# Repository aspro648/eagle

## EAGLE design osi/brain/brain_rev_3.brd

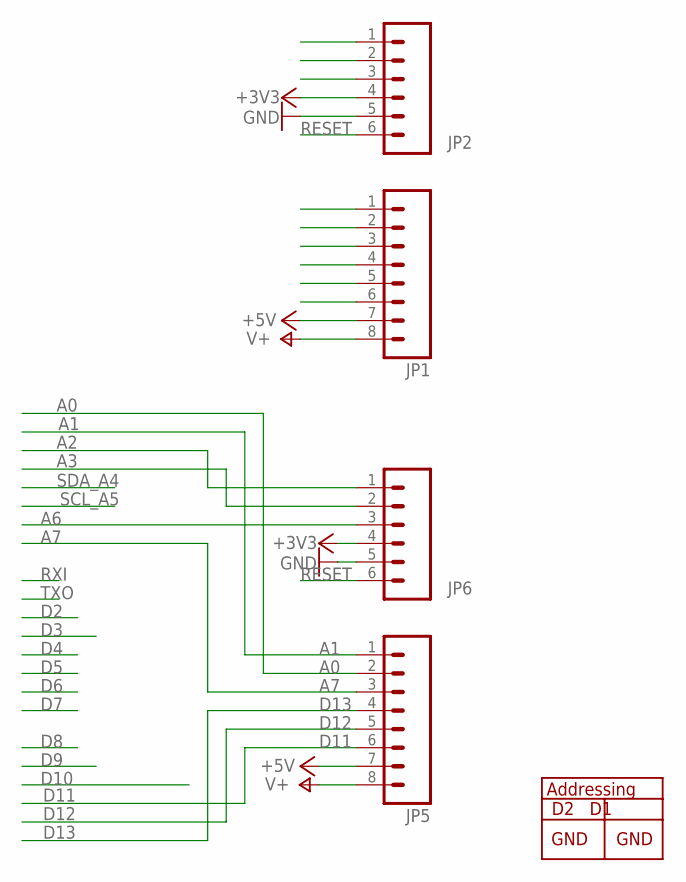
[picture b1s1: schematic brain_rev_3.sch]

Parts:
JP1, JP5: M081X08; 1X08
JP2, JP6: M06SIP; 1X06

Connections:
+3V3: JP2.4, JP6.4
+5V: JP1.7, JP5.7
A0: JP5.2
A1: JP5.1
A2: JP6.1
A3: JP6.2
A6: JP6.3
A7: JP5.3
D11: JP5.6
D12: JP5.5
D13: JP5.4
GND: JP2.5, JP6.5
RESET: JP2.6, JP6.6
V+: JP1.8, JP5.8

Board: 2 copper layers, 4 parts (0 on the bottom side), 5 nets, no tracks yet.

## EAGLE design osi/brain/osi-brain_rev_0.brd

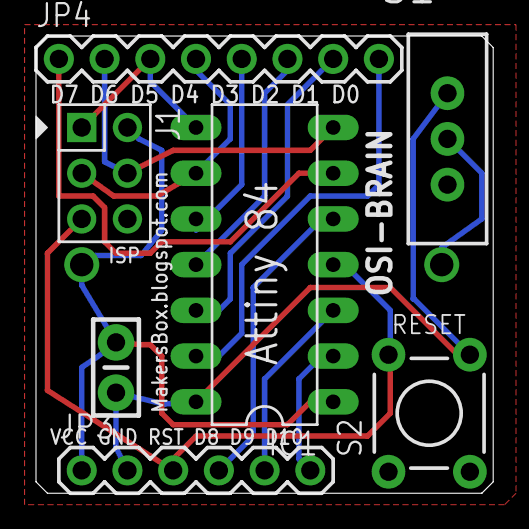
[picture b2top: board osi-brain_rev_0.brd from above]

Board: 2 copper layers, 25.4 x 25.4 mm, 8 parts (0 on the bottom side), 15 nets.

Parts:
BAT: BATTCOM_20MM_PTH
C1: CAP-PTH-SMALL-KIT
IC1: TINY24/44/84-PU; DIL14
J1: CON_HEADER_PRG_AVR_ICSP-PTH; HEADER_PRG_2X03
JP3: 1X06
JP4: 1X08
S1: SWITCH-SPDT
S2: TACTILE-PTH

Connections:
D0: IC1.13, JP4.8
D1: IC1.12, JP4.7
D2: IC1.11, JP4.6
D3: IC1.10, JP4.5
D4: IC1.9, J1.3, JP4.4
D5: IC1.8, J1.1, JP4.3
D6: IC1.7, J1.4, JP4.2
D7: IC1.6, JP4.1
D8: IC1.5, JP3.4
D9: IC1.3, JP3.5
D10: IC1.2, JP3.6
GND: C1.1, IC1.14, JP3.2, S1.1, S2.4
unnamed: BAT.1, S1.2
RESET: IC1.4, J1.5, JP3.3, S2.2
VCC: BAT.2, C1.2, IC1.1, J1.2, JP3.1

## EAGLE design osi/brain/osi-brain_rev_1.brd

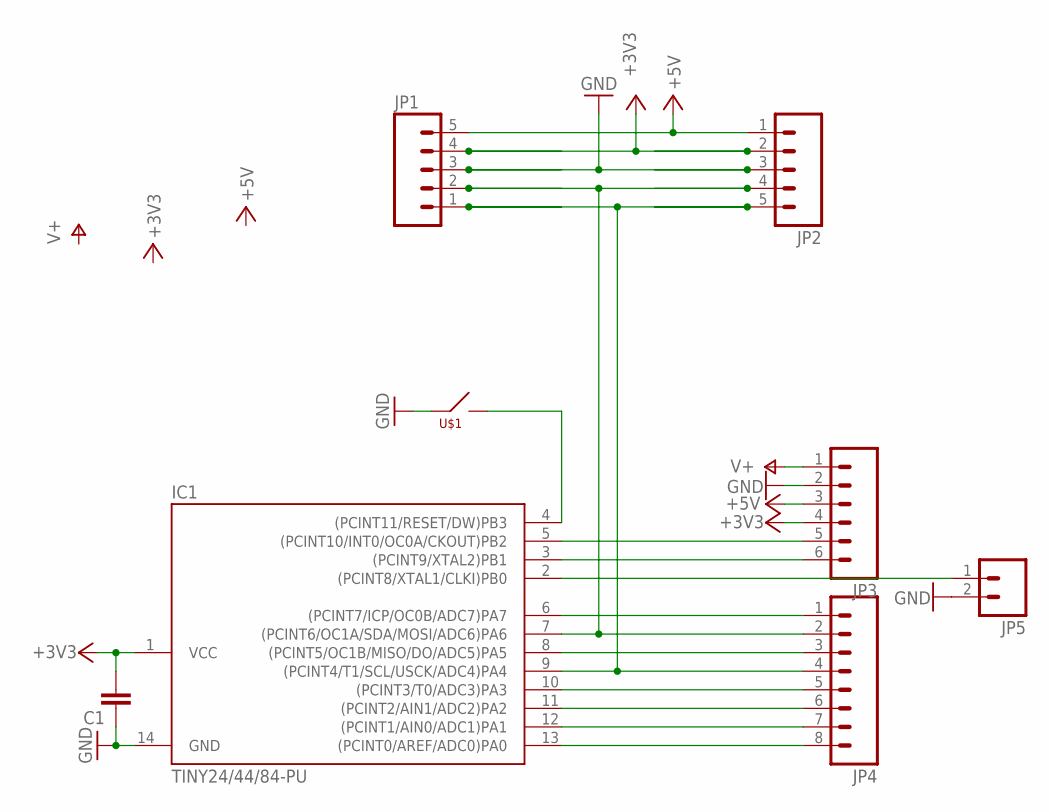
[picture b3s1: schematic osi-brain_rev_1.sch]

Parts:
C1: CAPKIT; CAP-PTH-SMALL-KIT
IC1: TINY24/44/84-PU; DIL14
JP1, JP2: M05PTH; 1X05
JP3: M06SIP; 1X06
JP4: M081X08; 1X08
JP5: M021X02_NO_SILK; 1X02_NO_SILK
U$1: PTS635_SWITCH

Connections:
+3V3: C1.2, IC1.1 (VCC), JP1.4, JP2.2, JP3.4
+5V: JP1.5, JP2.1, JP3.3
AREF_D0: IC1.13 ((PCINT0/AREF/ADC0)PA0), JP4.8
D1: IC1.12 ((PCINT1/AIN0/ADC1)PA1), JP4.7
D2: IC1.11 ((PCINT2/AIN1/ADC2)PA2), JP4.6
D3: IC1.10 ((PCINT3/T0/ADC3)PA3), JP4.5
D5: IC1.8 ((PCINT5/OC1B/MISO/DO/ADC5)PA5), JP4.3
D7: IC1.6 ((PCINT7/ICP/OC0B/ADC7)PA7), JP4.1
D8: IC1.5 ((PCINT10/INT0/OC0A/CKOUT)PB2), JP3.5
D9: IC1.3 ((PCINT9/XTAL2)PB1), JP3.6
D10: IC1.2 ((PCINT8/XTAL1/CLKI)PB0), JP5.1
GND: C1.1, IC1.14 (GND), JP1.3, JP2.3, JP3.2, JP5.2, U$1.P$1
RESET: IC1.4 ((PCINT11/RESET/DW)PB3), U$1.P$2
SCL_D4: IC1.9 ((PCINT4/T1/SCL/USCK/ADC4)PA4), JP1.1, JP2.5, JP4.4
SDA_D6: IC1.7 ((PCINT6/OC1A/SDA/MOSI/ADC6)PA6), JP1.2, JP2.4, JP4.2
V+: JP3.1

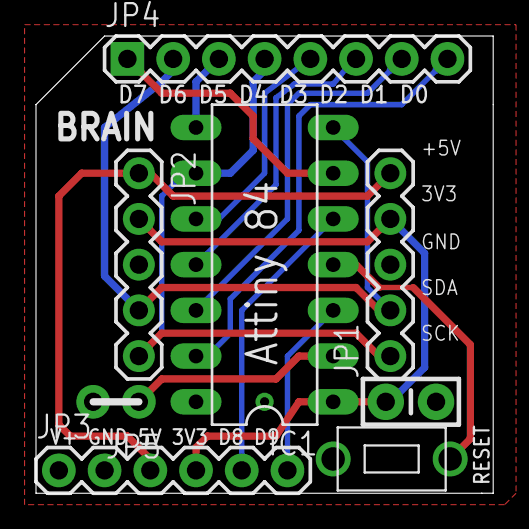
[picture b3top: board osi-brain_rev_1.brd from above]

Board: 2 copper layers, 25.4 x 25.4 mm, 8 parts (0 on the bottom side), 15 nets.

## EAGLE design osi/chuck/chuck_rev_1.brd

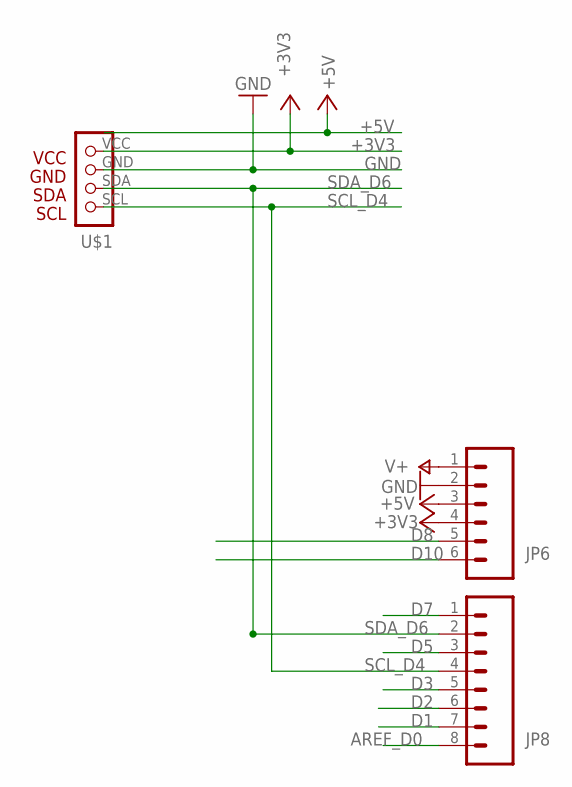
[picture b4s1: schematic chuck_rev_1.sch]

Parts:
JP6: M06SIP; 1X06
JP8: M081X08; 1X08
U$1: NUNCHUCKCHUCK; CONN

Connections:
+3V3: JP6.4, U$1.VCC
+5V: JP6.3
AREF_D0: JP8.8
D1: JP8.7
D2: JP8.6
D3: JP8.5
D5: JP8.3
D7: JP8.1
D8: JP6.5
D10: JP6.6
GND: JP6.2, U$1.GND
SCL_D4: JP8.4, U$1.SCL
SDA_D6: JP8.2, U$1.SDA
V+: JP6.1

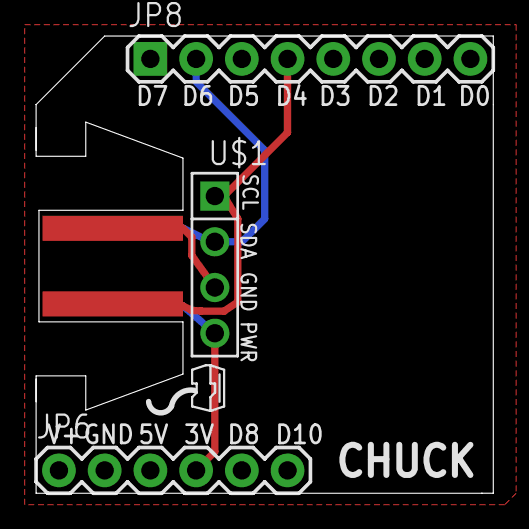
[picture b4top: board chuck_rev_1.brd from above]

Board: 2 copper layers, 25.4 x 25.4 mm, 3 parts (0 on the bottom side), 4 nets.

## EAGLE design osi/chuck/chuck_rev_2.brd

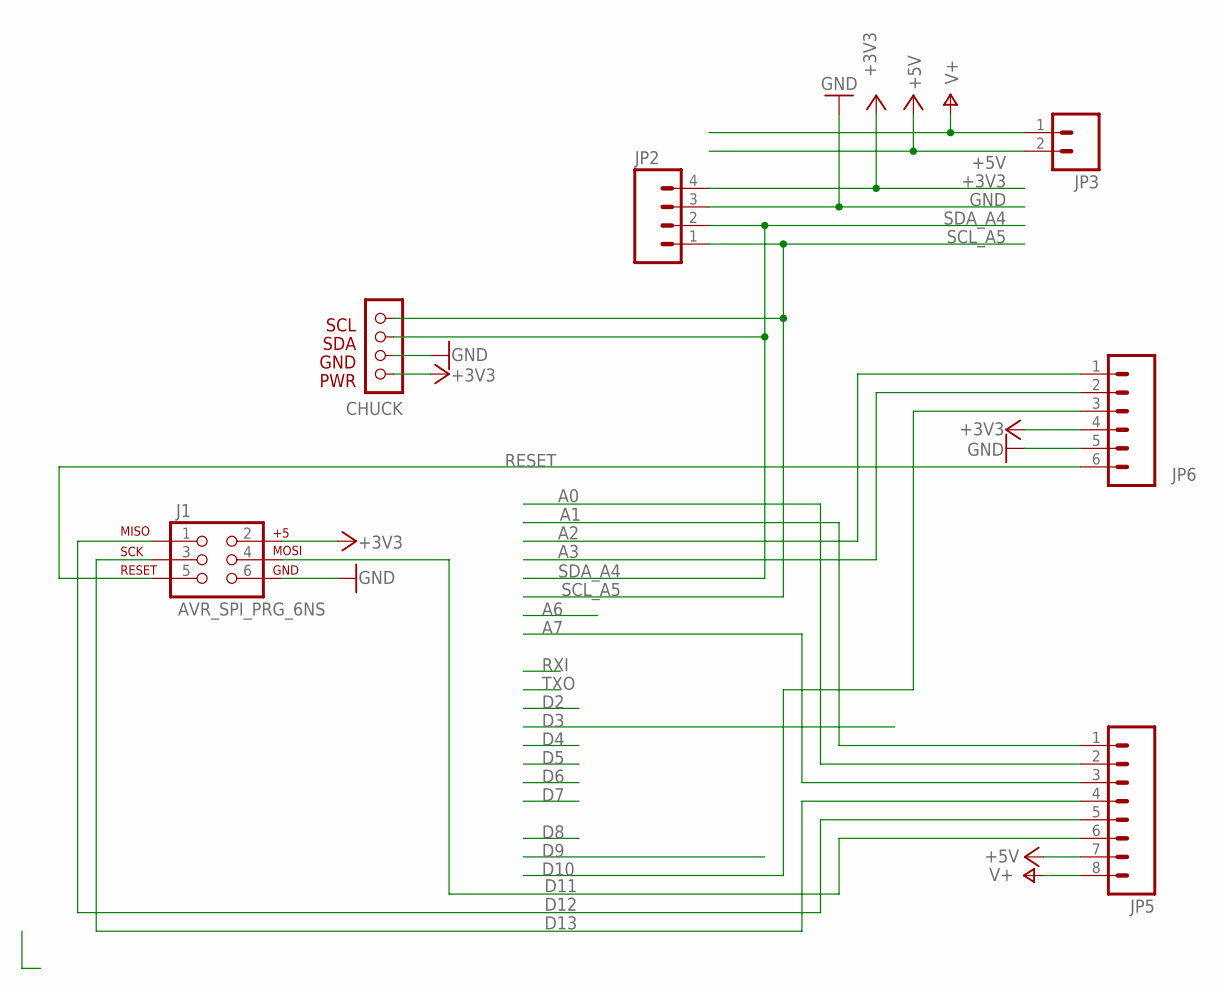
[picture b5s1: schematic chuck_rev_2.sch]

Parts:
CHUCK: NUNCHUCK; CONN
J1: AVR_SPI_PRG_6NS; 2X3-NS
JP2: M04PTH; 1X04
JP3: M02PTH; 1X02
JP5: M081X08; 1X08
JP6: M06SIP; 1X06

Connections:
+3V3: CHUCK.PWR, J1.2, JP2.4, JP6.4
+5V: JP3.2, JP5.7
A0: JP5.2
A1: JP5.1
A2: JP6.1
A3: JP6.2
A7: JP5.3
D10: JP6.3
D11: J1.4, JP5.6
D12: J1.1, JP5.5
D13: J1.3, JP5.4
GND: CHUCK.GND, J1.6, JP2.3, JP6.5
RESET: J1.5, JP6.6
SCL_A5: CHUCK.SCL, JP2.1
SDA_A4: CHUCK.SDA, JP2.2
V+: JP3.1, JP5.8

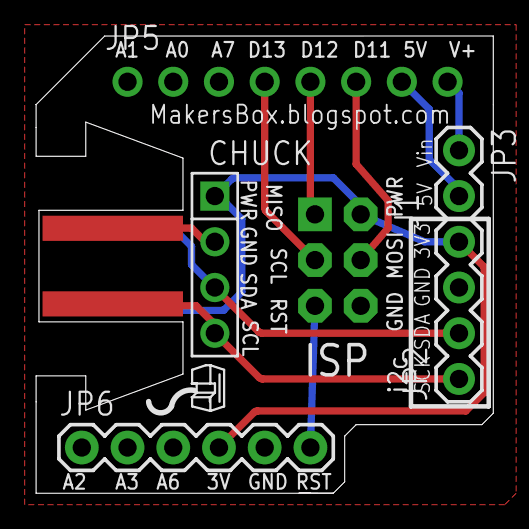
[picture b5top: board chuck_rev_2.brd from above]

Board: 2 copper layers, 25.4 x 25.4 mm, 6 parts (0 on the bottom side), 10 nets.

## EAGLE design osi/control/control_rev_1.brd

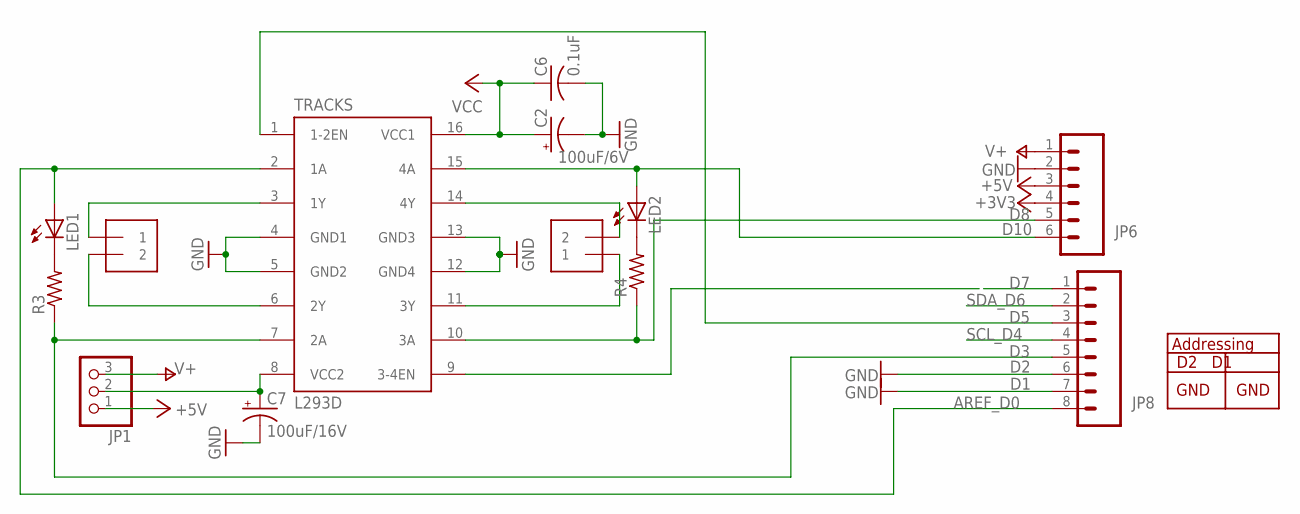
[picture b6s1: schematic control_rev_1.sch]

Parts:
C2: 100uF/6V; E2,5-5
C6: 0.1uF; C025-025X050
C7: 100uF/16V; E2,5-6
J1, J2: 1X2-3.5MM
JP1: PINHD-1X3; 1X03
JP6: M06SIP; 1X06
JP8: M081X08; 1X08
LED1, LED2: LED3MM
R3, R4: R-US_0204/2V; 0204V
TRACKS: L293D; DIL16

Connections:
+3V3: JP6.4
+5V: JP1.1, JP6.3
AREF_D0: JP8.8, LED1.A, TRACKS.2 (1A)
D1: JP8.7
D2: JP8.6
D3: JP8.5, R3.1, TRACKS.7 (2A)
D5: JP8.3, TRACKS.1 (1-2EN)
D7: JP8.1
D8: JP6.5, R4.1, TRACKS.10 (3A)
D10: JP6.6, LED2.A, TRACKS.15 (4A)
GND: C2.-, C6.2, C7.-, JP6.2, TRACKS.4 (GND1), TRACKS.5 (GND2), TRACKS.12 (GND4), TRACKS.13 (GND3)
unnamed: J1.1, TRACKS.3 (1Y)
unnamed: J2.2, TRACKS.14 (4Y)
unnamed: J1.2, TRACKS.6 (2Y)
unnamed: J2.1, TRACKS.11 (3Y)
unnamed: LED1.K (C), R3.2
unnamed: LED2.K (C), R4.2
unnamed: C7.+, JP1.2, TRACKS.8 (VCC2)
SCL_D4: JP8.4
SDA_D6: JP8.2
V+: JP1.3, JP6.1
VCC: C2.+, C6.1, TRACKS.16 (VCC1)

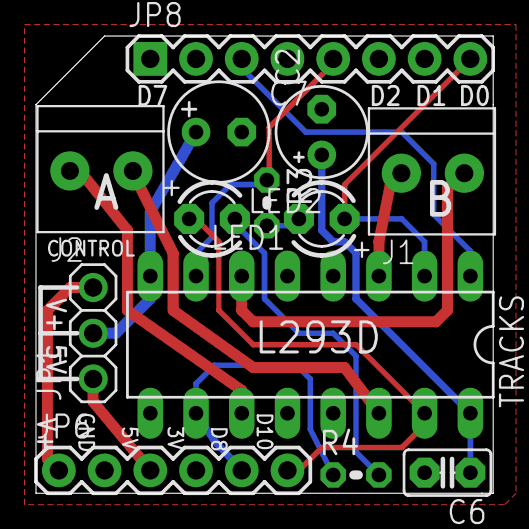
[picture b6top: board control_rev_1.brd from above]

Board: 2 copper layers, 25.4 x 25.4 mm, 13 parts (0 on the bottom side), 16 nets.

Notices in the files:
parts and their libraries:
SparkFun: Licensing: CC v3.0 Share-Alike You are welcome to use this library for commercial purposes.
